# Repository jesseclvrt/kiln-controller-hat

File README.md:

# Kiln Controller HATs
HATs to implement [jbruce12000/kiln-controller](https://github.com/jbruce12000/kiln-controller) in Raspberry Pi Zero W form-factor.

## Two PCBs
There are two PCBs for controlling the MAX31855 in either software (right) or hardware(left) SPI. The software PCB has a cleaner layout with traces, but is allegedy slower.

## BOM
In addition to the regular materials for jbruce12000's controller, you will need:

* 1x6 socket header with 2.54mm pitch (MAX31855)
* 2x20 socket header with 2.54mm pitch (RPi GPIO)
* 1x2 pin or socket header with 2.54 pitch (SSR)

## Assembly
Ensure the GPIO header gets soldered to the back of the board. Solder in the resistors, transistor, and socket headers. The hat is attached to use the entire GPIO header, although it only uses a small number of pins.

The MAX31855 is attached upside down onto the board. This is because I already soldered my pins rightside up and I didn't want to resolder or buy a new MAX. The design would need to be changed to flip the MAX header around for a cleaner looking install.

Remember to update your config.py to reflect which pins you are using. Hardware SPI should define no pins. The software SPI board uses these pins:

| Physical Pin | GPIO | Connected to | config.py line        |
| ------------ | ---- | ------------ |-----------------------|
| 23           | 11   | MAX31855 CLK | spi_sclk = board.D11  |
| 27           | 0    | MAX31855 CS  | spi_cs = board.D0     |
| 31           | 6    | MAX31855 DO  | spi_miso = board.D6   |
| 13           | 27   | SSR Control  | gpio_heat = board.D27 |

Set spi_mosi (serial input) to any unused pin, such as D10.

The board has the same dimensions as the Raspberry Pi Zero W, because that's the device I happened to have for this project. Drill holes are aligned to match that device, so maybe someone could make a nice 3D printed case for the whole assembly. Due to this, the board does have a lot of unused space, so the design can also be adjusted to save some manufacturing cost. Alternatively, maybe some additional features could be added, although I don't have the electronics skill for that.

## Thanks
Thank you [jbruce12000](https://github.com/jbruce12000) for reviving dead analog kilns with Raspberry Pi magic, and [Tech Explorations](https://techexplorations.com/) for teaching me the basics of KiCAD. These are my first PCB designs, so feedback would be welcome.

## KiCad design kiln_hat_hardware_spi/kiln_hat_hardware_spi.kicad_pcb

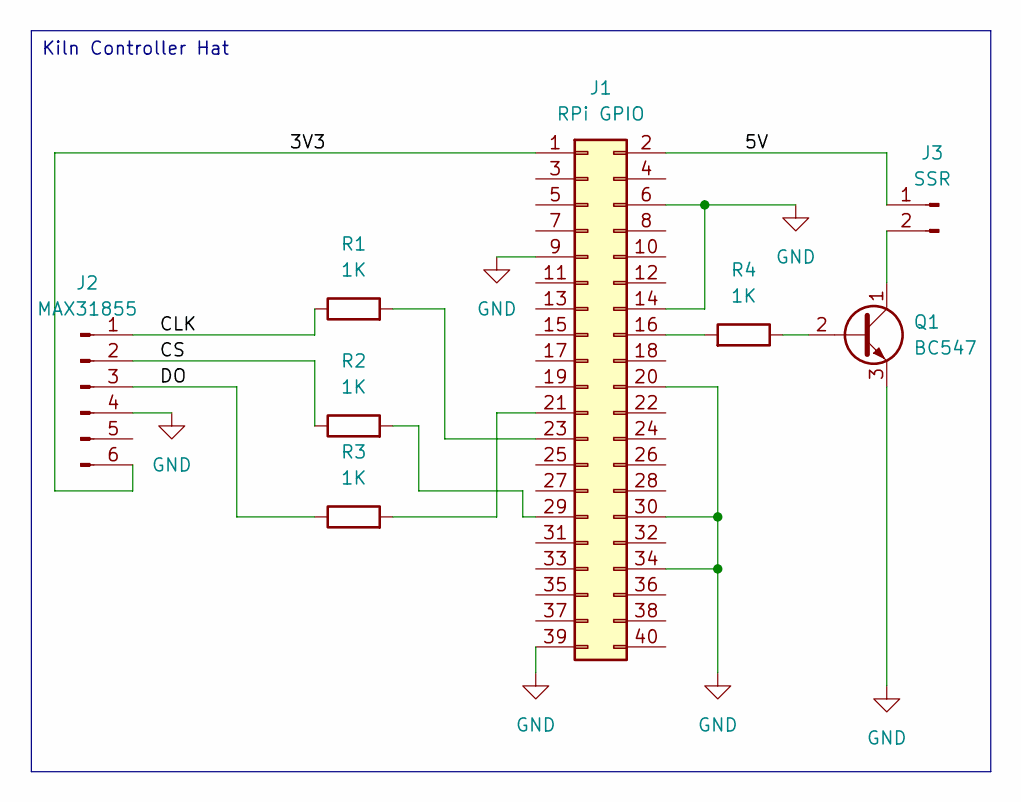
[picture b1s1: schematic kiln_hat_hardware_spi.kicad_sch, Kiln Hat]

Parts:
J1: RPi GPIO; PinSocket_2x20_P2.54mm_Vertical
J2: MAX31855; PinSocket_1x06_P2.54mm_Vertical
J3: SSR; PinHeader_1x02_P2.54mm_Vertical
Q1: BC547; TO-92_Inline
R1, R2, R3, R4: 1K; R_Axial_DIN0309_L9.0mm_D3.2mm_P12.70mm_Horizontal

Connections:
/3V3: J1.1, J2.6
/5V: J1.2, J3.1
/CLK: J2.1, R1.1
/CS: J2.2, R2.1
/DO: J2.3, R3.1
GND: J1.6, J1.9, J1.14, J1.20, J1.30, J1.34, J1.39, J2.4, Q1.3 (E)
unnamed: J1.16, R4.2
unnamed: J1.21, R3.2
unnamed: J1.23, R1.2
unnamed: J1.29, R2.2
unnamed: J3.2, Q1.1 (C)
unnamed: Q1.2 (B), R4.1

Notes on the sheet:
Kiln Controller Hat

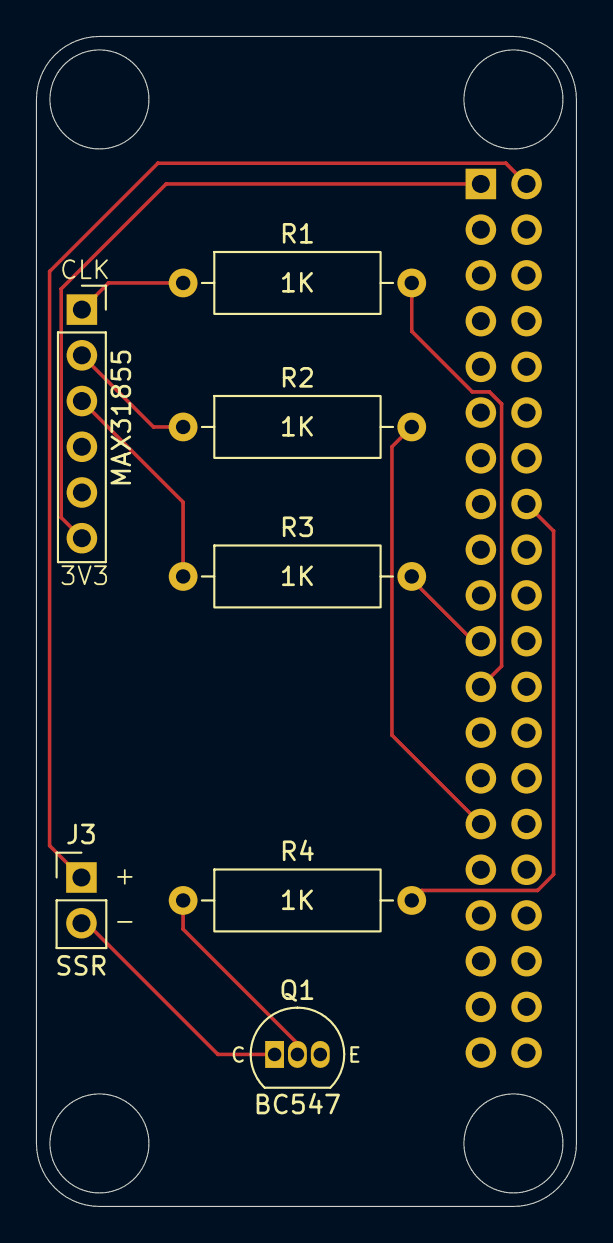
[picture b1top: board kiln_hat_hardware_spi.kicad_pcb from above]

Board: 2 copper layers, 30.0 x 65.0 mm, 8 parts (1 on the bottom side), 12 nets.

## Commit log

2025-11-23 Add link to jbruce12000/kiln-controller
2026-02-01 added config.py lines
2026-02-01 Delete kiln_hat_hardware_spi/gerbers.zip
    moved to releases
2026-02-01 Delete kiln_hat_software_spi/gerbers.zip
    moved to releases
2026-02-01 updating readme with image of PCBs and links to special mentions
2026-02-01 add newline
